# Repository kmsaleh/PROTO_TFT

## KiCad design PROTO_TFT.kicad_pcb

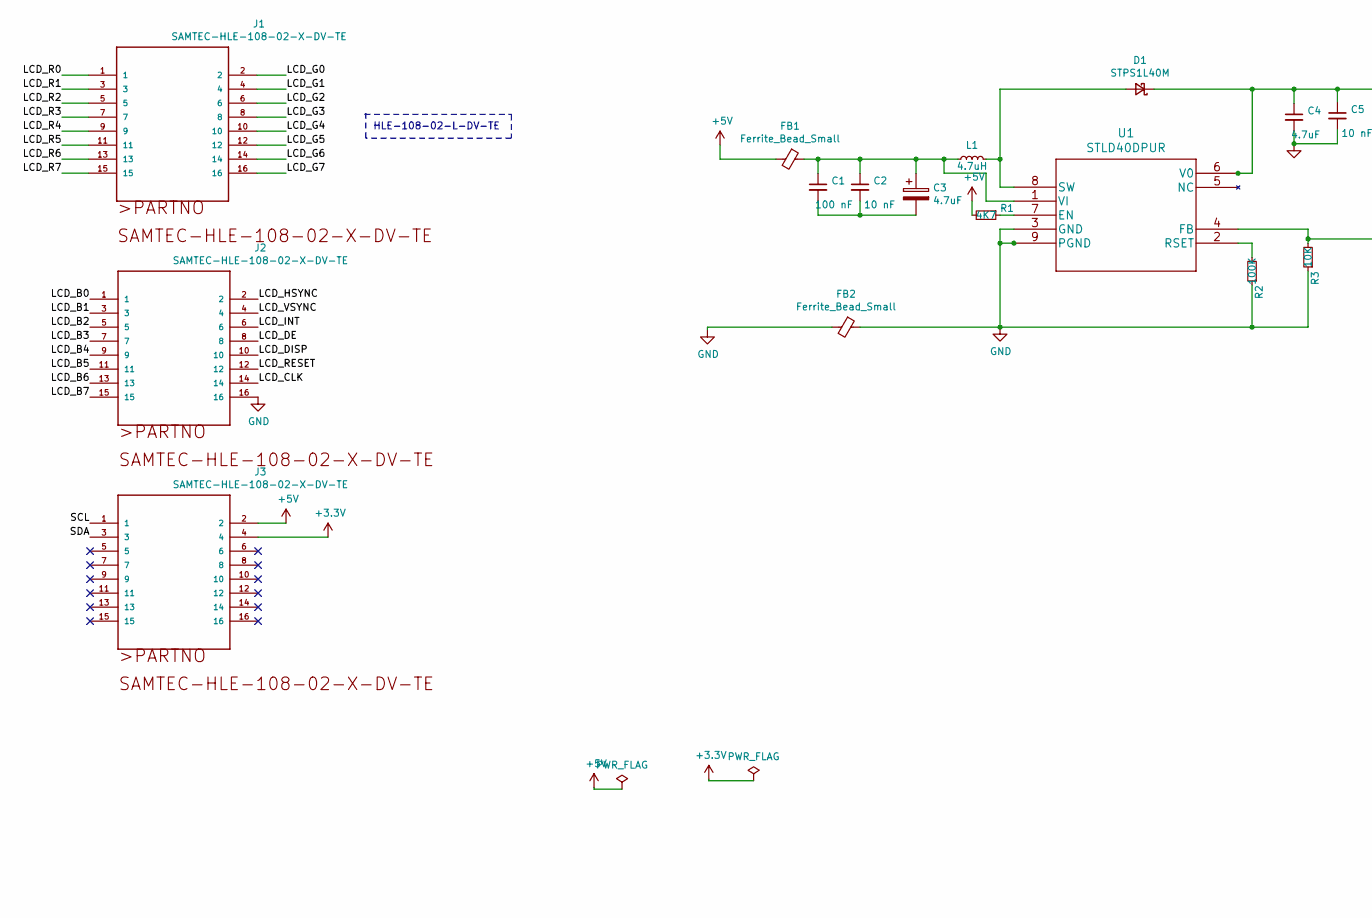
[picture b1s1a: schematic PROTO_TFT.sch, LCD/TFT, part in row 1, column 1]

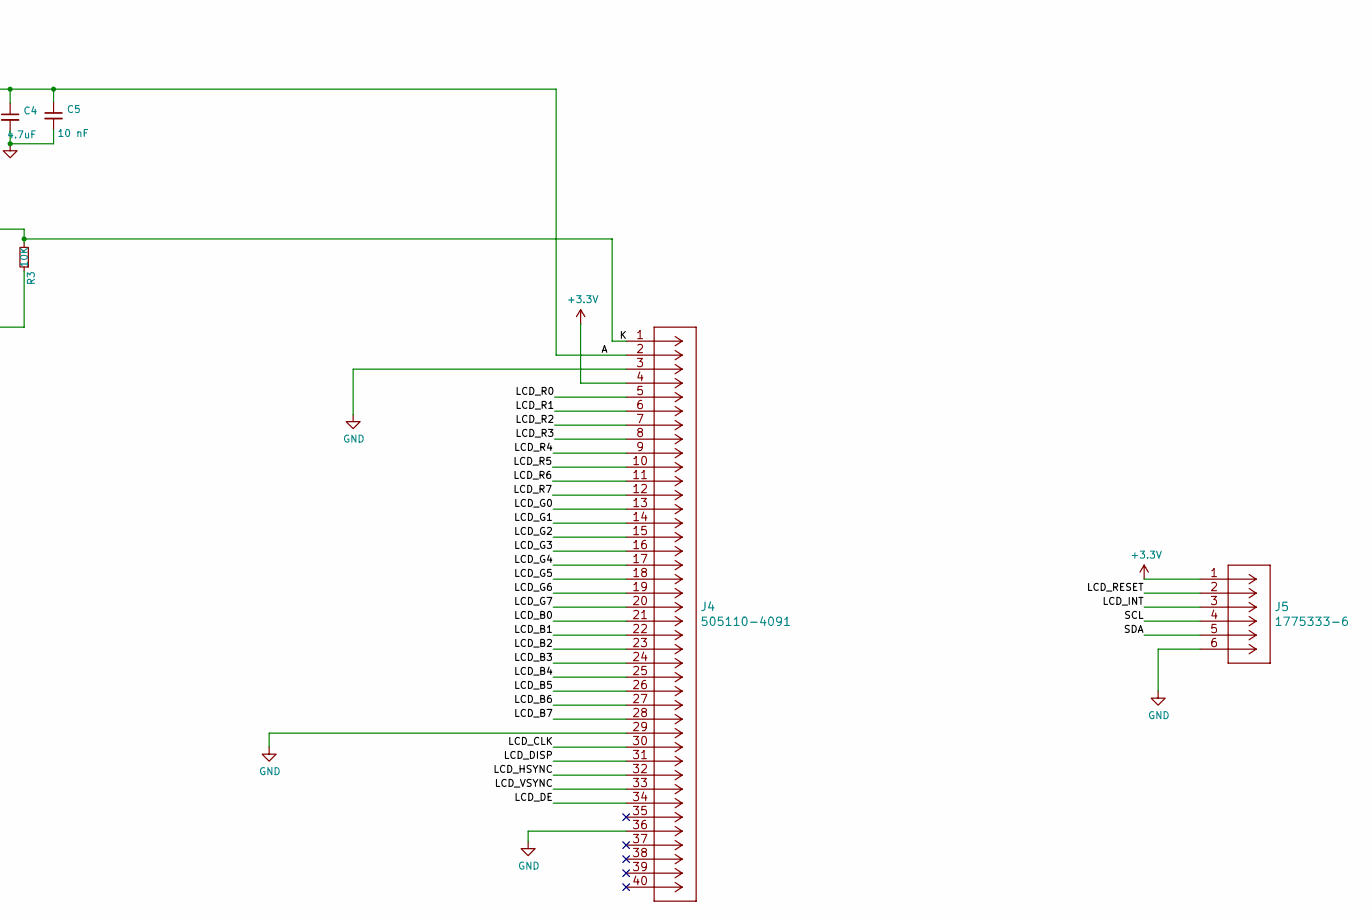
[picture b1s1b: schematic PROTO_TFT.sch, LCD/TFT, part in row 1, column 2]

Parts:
C1: 100 nF; C_0805_2012Metric
C2, C5: 10 nF; C_0805_2012Metric
C3, C4: 4.7uF; C_0805_2012Metric
D1: STPS1L40M
FB1, FB2: Ferrite_Bead_Small; L_0805_2012Metric
J1, J2, J3: SAMTEC-HLE-108-02-X-DV-TE
J4: 505110-4091
J5: 1775333-6
L1: 4.7uH; INDC3030X200N
R1: 4K7; R_0805_2012Metric
R2: 100K; R_0805_2012Metric
R3: 10K; R_0805_2012Metric
U1: STLD40DPUR

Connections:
+3V3: J3.4, J4.4, J5.1
+5V: FB1.2, J3.2, R1.2
/A: C4.1, C5.1, D1.1 (K), J4.2, U1.6 (V0)
/K: J4.1, R3.2, U1.4 (FB)
/LCD_B0: J2.1, J4.21
/LCD_B1: J2.3, J4.22
/LCD_B2: J2.5, J4.23
/LCD_B3: J2.7, J4.24
/LCD_B4: J2.9, J4.25
/LCD_B5: J2.11, J4.26
/LCD_B6: J2.13, J4.27
/LCD_B7: J2.15, J4.28
/LCD_CLK: J2.14, J4.30
/LCD_DE: J2.8, J4.34
/LCD_DISP: J2.10, J4.31
/LCD_G0: J1.2, J4.13
/LCD_G1: J1.4, J4.14
/LCD_G2: J1.6, J4.15
/LCD_G3: J1.8, J4.16
/LCD_G4: J1.10, J4.17
/LCD_G5: J1.12, J4.18
/LCD_G6: J1.14, J4.19
/LCD_G7: J1.16, J4.20
/LCD_HSYNC: J2.2, J4.32
/LCD_INT: J2.6, J5.3
/LCD_R0: J1.1, J4.5
/LCD_R1: J1.3, J4.6
/LCD_R2: J1.5, J4.7
/LCD_R3: J1.7, J4.8
/LCD_R4: J1.9, J4.9
/LCD_R5: J1.11, J4.10
/LCD_R6: J1.13, J4.11
/LCD_R7: J1.15, J4.12
/LCD_RESET: J2.12, J5.2
/LCD_VSYNC: J2.4, J4.33
/SCL: J3.1, J5.4
/SDA: J3.3, J5.5
GND: C4.2, C5.2, FB2.1, FB2.2, J2.16, J4.3, J4.29, J4.36, J5.6, R2.1, R3.1, U1.3 (GND), U1.9 (PGND)
unnamed: C1.1, C2.1, C3.1, FB1.1, L1.1, U1.1 (VI)
unnamed: C1.2, C2.2, C3.2
unnamed: D1.2 (A), L1.2, U1.8 (SW)
unnamed: R1.1, U1.7 (EN)
unnamed: R2.2, U1.2 (RSET)

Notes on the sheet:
HLE-108-02-L-DV-TE

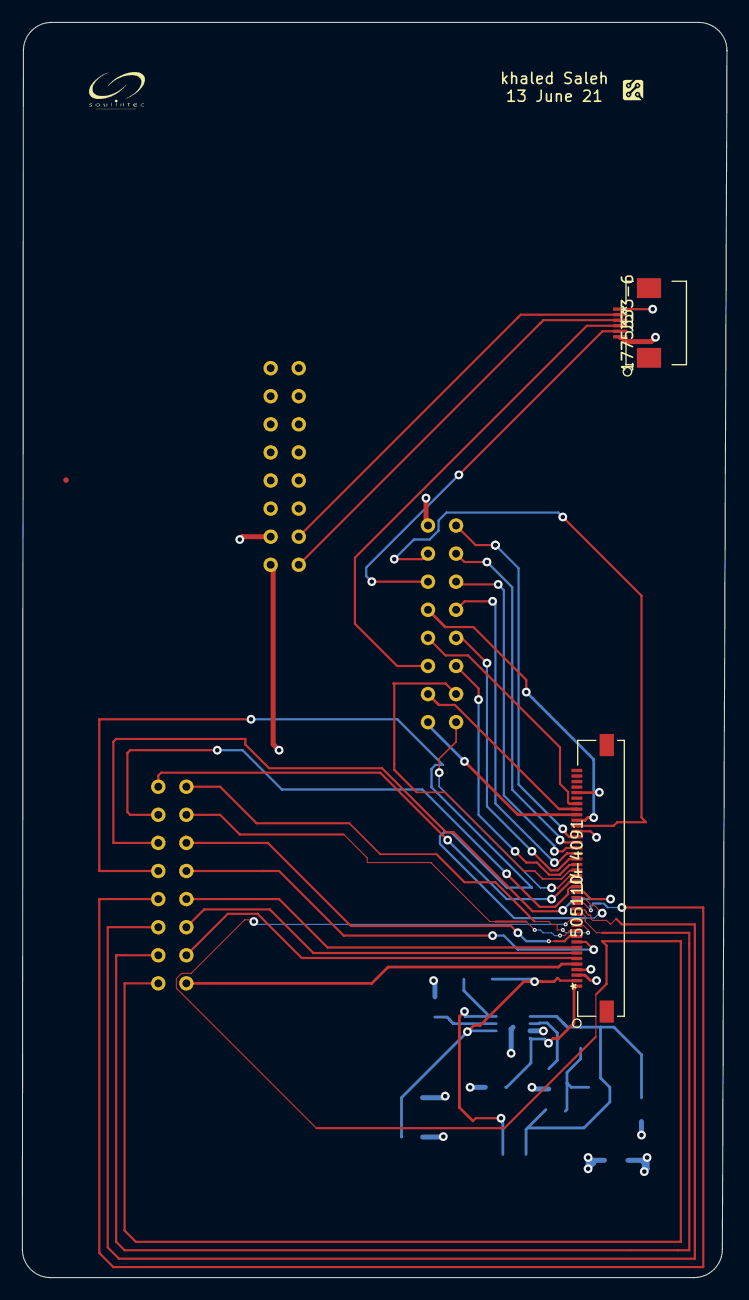
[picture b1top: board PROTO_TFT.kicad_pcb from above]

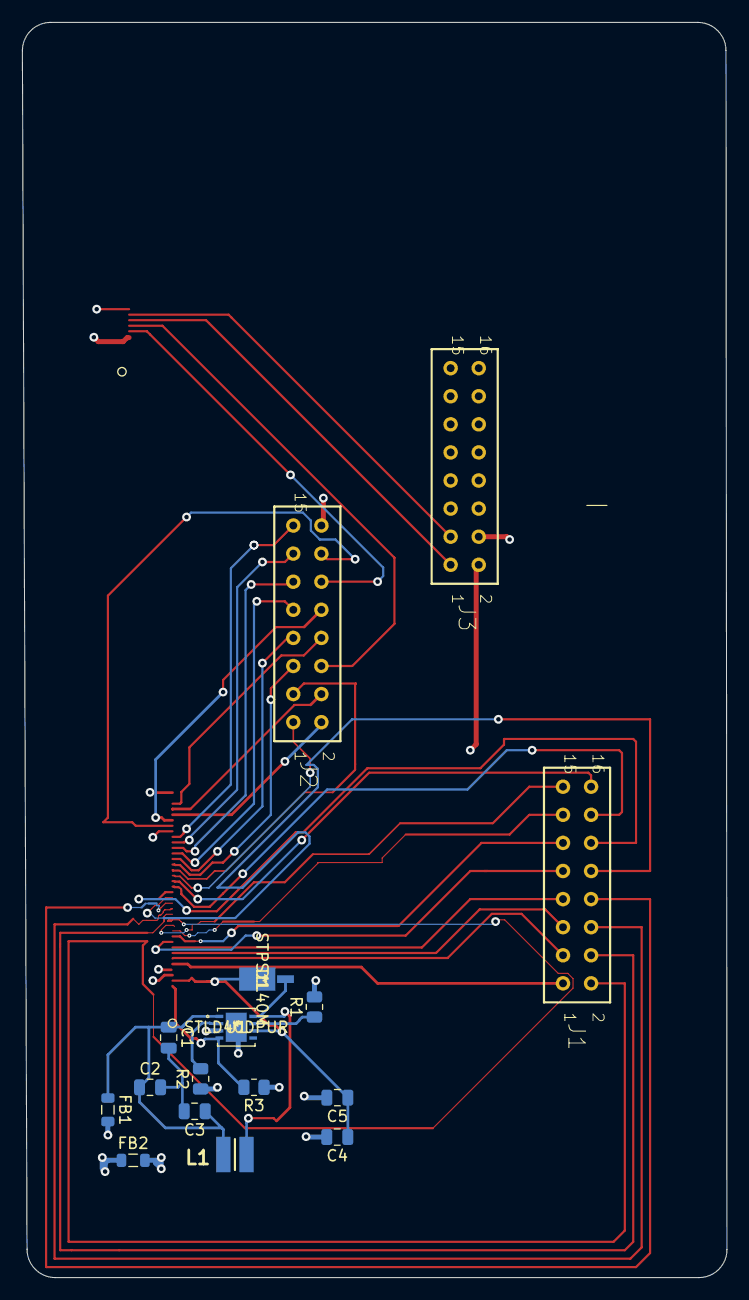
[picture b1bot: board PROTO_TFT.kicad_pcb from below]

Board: 4 copper layers, 63.7 x 113.5 mm, 19 parts (16 on the bottom side), 43 nets.

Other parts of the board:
*: Fiducial_0.5mm_Mask1.5mm

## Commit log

2021-08-08 second commit
2021-08-08 3rd commit
2021-08-08 4th commit

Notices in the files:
parts and their libraries:
Copyright 2021 Accelerated Designs. All rights reserved.
